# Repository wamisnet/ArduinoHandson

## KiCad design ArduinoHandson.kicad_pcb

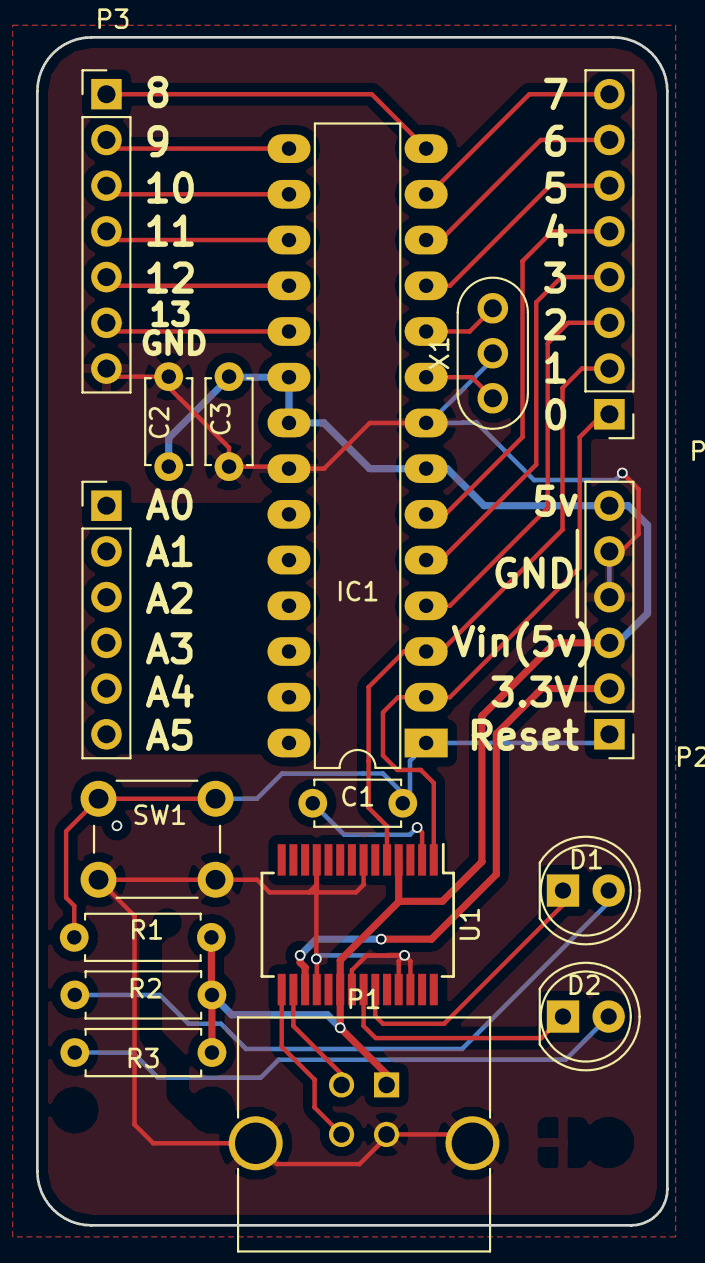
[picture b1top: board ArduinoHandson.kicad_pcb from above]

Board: 2 copper layers, 35.0 x 66.0 mm, 17 parts (0 on the bottom side), 33 nets.

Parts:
C1, C3: 0.1uF; C_Disc_D4.7mm_W2.5mm_P5.00mm
C2: 10uF; C_Disc_D4.7mm_W2.5mm_P5.00mm
D1: RX; LED_D5.0mm
D2: TX; LED_D5.0mm
IC1: ATMEGA328-P; DIP-28_W7.62mm_LongPads
P1: USB_B; USB_B_MUSB_Straight
P2: Power; Socket_Strip_Straight_1x06_Pitch2.54mm
P3: Digital2; Socket_Strip_Straight_1x07_Pitch2.54mm
P4: Analog; Socket_Strip_Straight_1x06_Pitch2.54mm
P5: Digital1; Socket_Strip_Straight_1x08_Pitch2.54mm
R1: 10k; R_Axial_DIN0207_L6.3mm_D2.5mm_P7.62mm_Horizontal
R2, R3: 500; R_Axial_DIN0207_L6.3mm_D2.5mm_P7.62mm_Horizontal
SW1: SW_PUSH; SW_PUSH_6mm_h5mm
U1: FT232RL; SSOP-28_5.3x10.2mm_Pitch0.65mm
X1: CRYSTAL; Resonator-3pin_w8.0mm_h3.5mm

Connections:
+3V3: P2.2, U1.17
+5V: C2.1, C3.1, IC1.7, IC1.20, IC1.21, P1.1, P2.3, P2.6, R1.2, R2.1, R3.1, U1.4, U1.20
/A0: IC1.23, P4.1
/A1: IC1.24, P4.2
/A2: IC1.25, P4.3
/A3: IC1.26, P4.4
/A4: IC1.27, P4.5
/A5: IC1.28, P4.6
/D0: IC1.2, P5.1, U1.1
/D1: IC1.3, P5.2, U1.5
/D2: IC1.4, P5.3
/D3: IC1.5, P5.4
/D4: IC1.6, P5.5
/D5: IC1.11, P5.6
/D6: IC1.12, P5.7
/D7: IC1.13, P5.8
/D8: IC1.14, P3.1
/D9: IC1.15, P3.2
/D10: IC1.16, P3.3
/D11: IC1.17, P3.4
/D12: IC1.18, P3.5
/D13: IC1.19, P3.6
/D+: P1.3, U1.15
/D-: P1.2, U1.16
/Reset: C1.2, IC1.1, P2.1, R1.1, SW1.1
/XTAL1: IC1.9, X1.1
/XTAL2: IC1.10, X1.3
GND: C2.2, C3.2, IC1.8, IC1.22, P1.4, P1.5, P2.4, P2.5, P3.7, SW1.2, U1.7, U1.11, U1.18, U1.21, U1.25, U1.26, X1.2
unnamed: C1.1, U1.2
unnamed: D1.1, U1.23
unnamed: D1.2, R2.2
unnamed: D2.1, U1.22
unnamed: D2.2, R3.2

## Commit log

2017-03-25 fast
2017-03-25 回路図途中
2017-03-25 回路図完成
2017-03-25 部品配置のみ
2017-03-25 配線のみ
2017-03-26 外形変更、文字表示対応
2017-03-26 ベタグランド
2017-03-27 配線図完成
2017-03-29 回路図完成形pdf
2017-03-29 回路図+配線図完成
2017-03-29 配線図開始
2017-03-29 関連づけ前
2017-03-29 ハンズオン開始時配布ファイル
